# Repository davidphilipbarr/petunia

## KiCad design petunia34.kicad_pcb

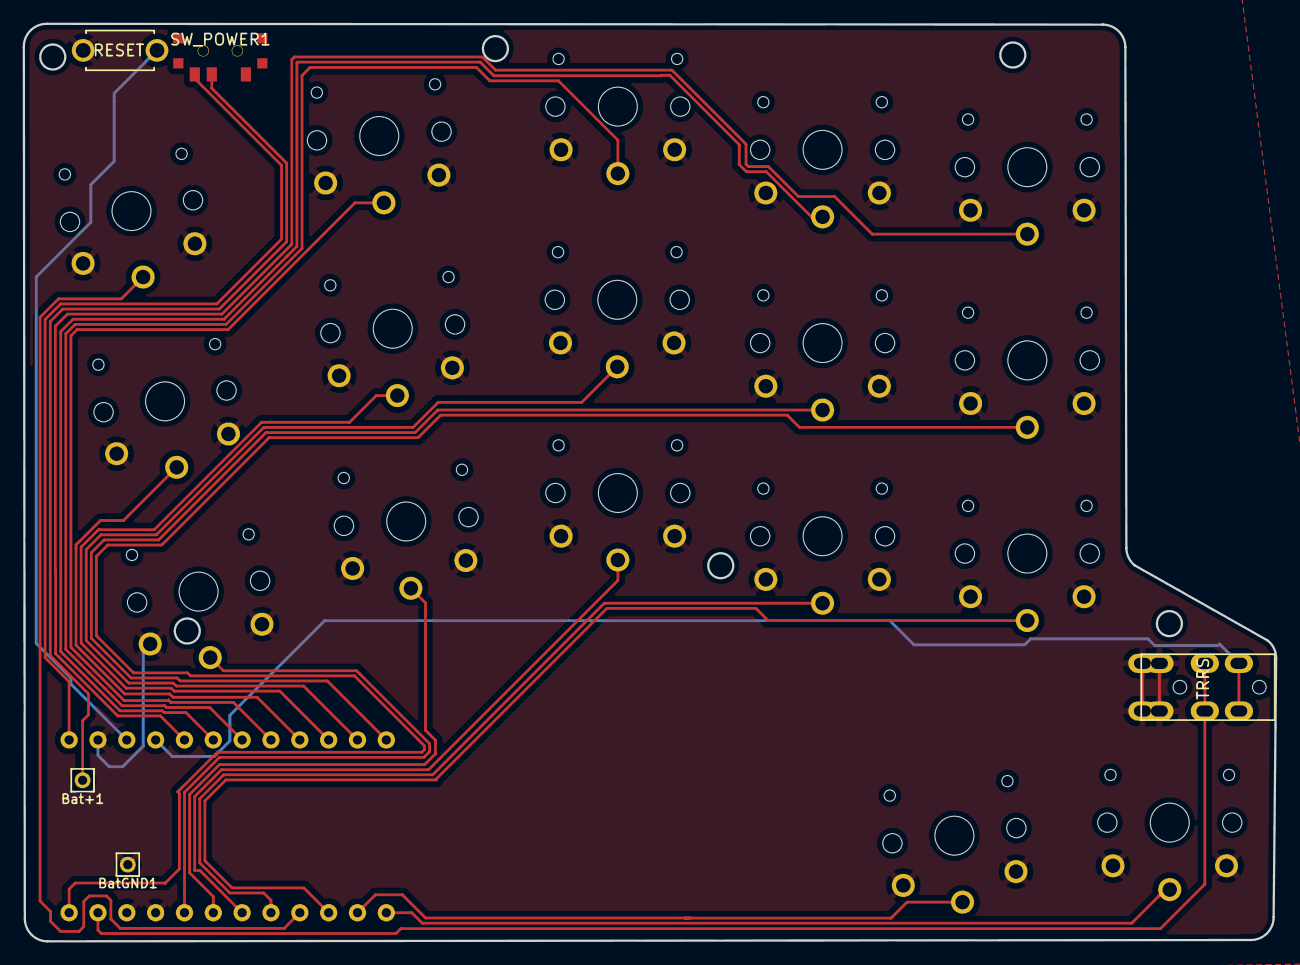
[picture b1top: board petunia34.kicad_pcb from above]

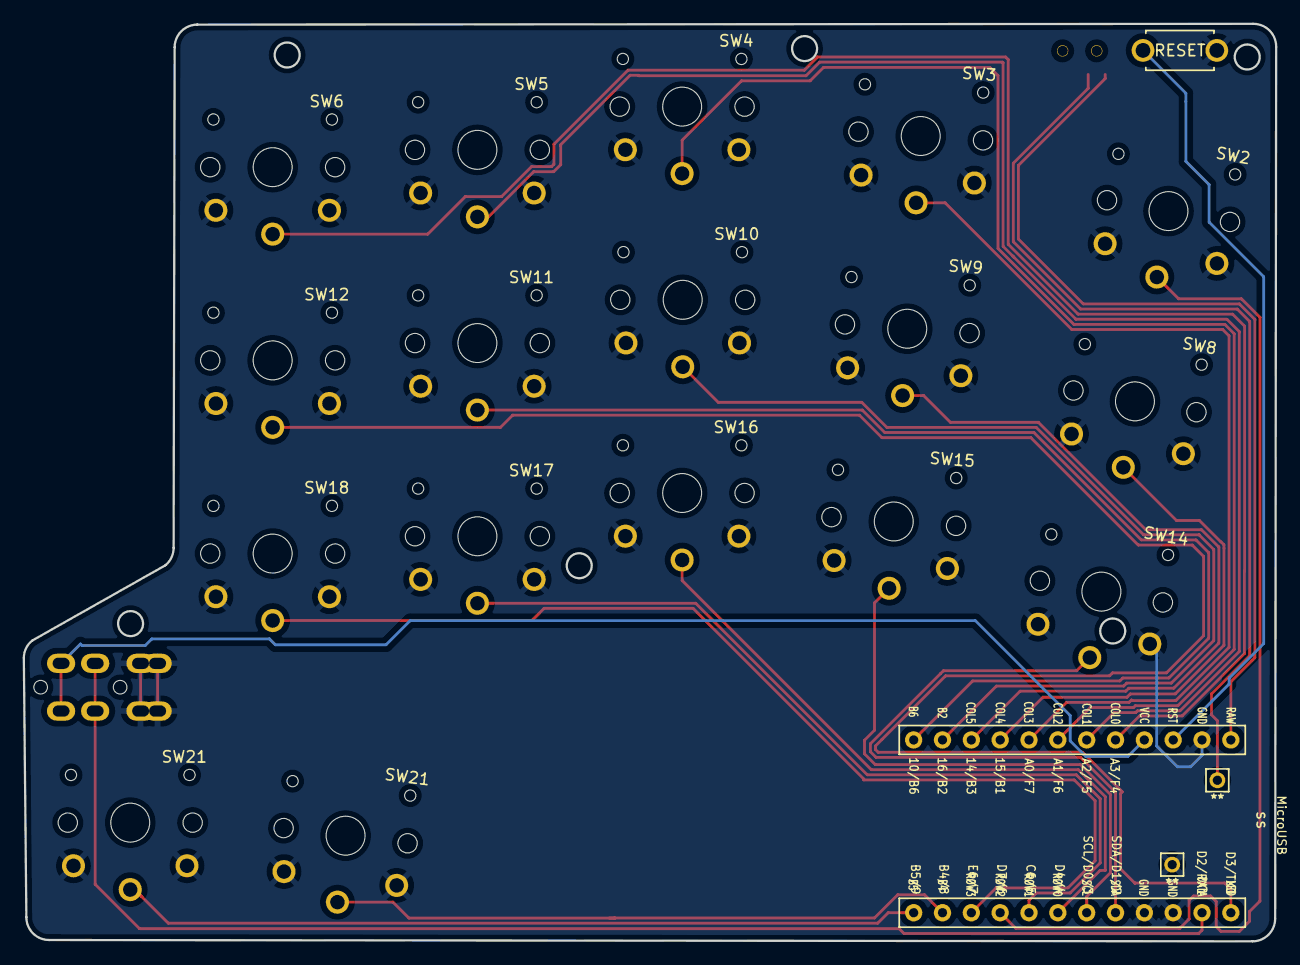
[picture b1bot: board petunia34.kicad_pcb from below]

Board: 2 copper layers, 110.3 x 80.8 mm, 23 parts (2 on the bottom side), 23 nets.

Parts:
Bat+1: MountingHole_Pad; 1pin_conn
BatGND1: MountingHole_Pad; 1pin_conn
J1: MJ-4PP-9; MJ-4PP-9_2side
RSW1: SW_Push; ResetSW
SW2, SW3, SW4, SW5, SW6, SW8, SW9, SW10, SW11, SW12, SW14, SW15, SW16, SW17, SW18, SW21, SW21#2: SW_Push; SW_PG1350_rev_DPB
SW_POWER1: SW_SPDT; SPDT_C128955
U1: ProMicro-kbd; ProMicro_v2_1side

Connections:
BT+: Bat+1.1, SW_POWER1.2
Switch1: SW2.1, U1.9
Switch2: SW3.1, U1.17
Switch3: SW4.1, U1.18
Switch4: SW5.1, U1.19
Switch5: SW6.1, U1.20
Switch6: SW8.1, U1.16
Switch7: SW9.1, U1.15
Switch8: SW10.1, U1.14
Switch9: SW11.1, U1.13
Switch10: SW12.1, U1.1
Switch11: SW14.1, U1.5
Switch12: SW15.1, U1.6
Switch13: SW16.1, U1.7
Switch14: SW17.1, U1.8
Switch15: SW18.1, U1.10
Switch16: SW21.1, U1.11
Switch17: SW21#2.1, U1.12
Switch18: J1.C, U1.2
gnd: BatGND1.1, J1.A, J1.D, RSW1.1, SW2.2, SW3.2, SW4.2, SW5.2, SW6.2, SW8.2, SW9.2, SW10.2, SW11.2, SW12.2, SW14.2, SW15.2, SW16.2, SW17.2, SW18.2, SW21.2, SW21#2.2, U1.3, U1.4, U1.23
raw: SW_POWER1.3, U1.24
reset: RSW1.2, U1.22
vcc: J1.B, U1.21

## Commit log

2021-11-24 phear the initial push
